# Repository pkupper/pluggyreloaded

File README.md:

# Pluggy Reloaded
Adapter Board for the Gigatron TTL Microcomputer

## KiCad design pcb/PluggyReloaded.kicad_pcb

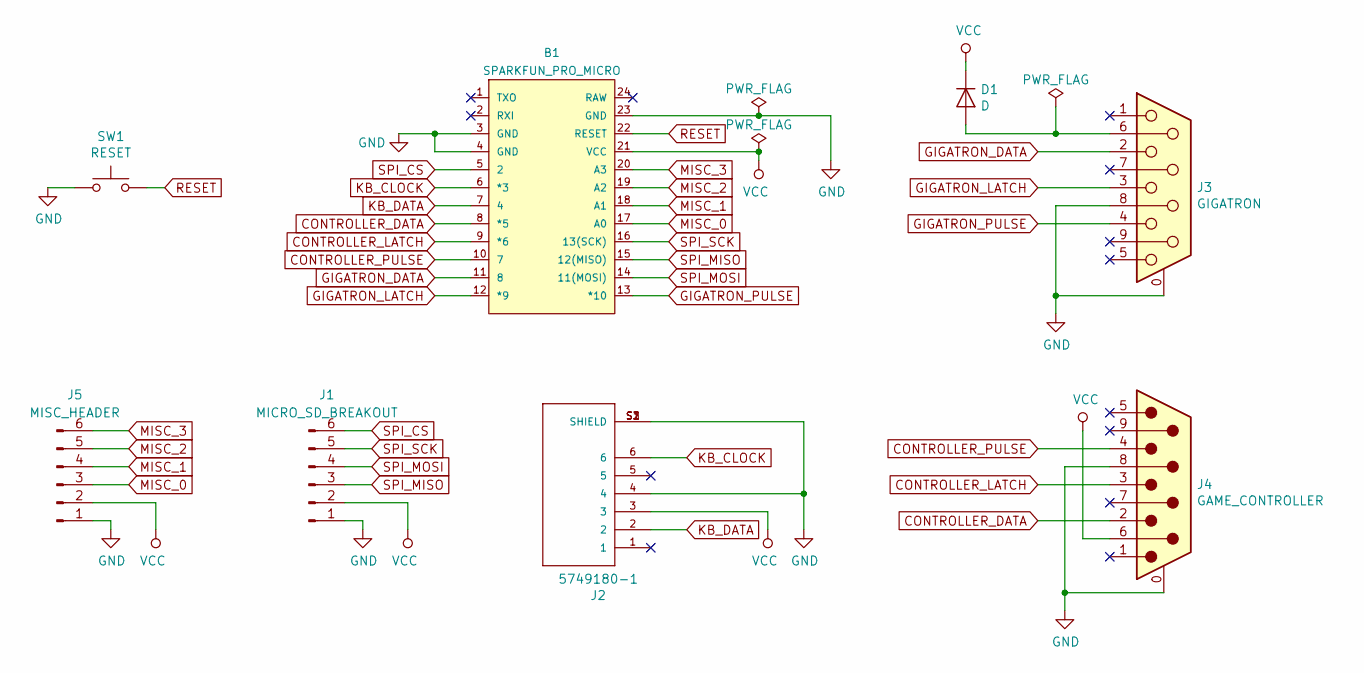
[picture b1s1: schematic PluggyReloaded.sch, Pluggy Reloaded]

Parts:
B1: SPARKFUN_PRO_MICRO
D1: D; D_DO-35_SOD27_P7.62mm_Horizontal
J1: MICRO_SD_BREAKOUT; PinHeader_1x06_P2.54mm_Vertical
J2: 5749180-1; TE_5749180-1
J3: GIGATRON; DSUB-9_Female_Horizontal_P2.77x2.84mm_EdgePinOffset9.90mm_H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
J4: GAME_CONTROLLER; DSUB-9_Male_Horizontal_P2.77x2.84mm_EdgePinOffset9.90mm_Hou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
J5: MISC_HEADER; PinHeader_1x06_P2.54mm_Vertical
SW1: RESET; SW_PUSH_6mm_H5mm

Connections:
CONTROLLER_DATA: B1.8 (*5), J4.2
CONTROLLER_LATCH: B1.9 (*6), J4.3
CONTROLLER_PULSE: B1.10 (7), J4.4
GIGATRON_DATA: B1.11 (8), J3.2
GIGATRON_LATCH: B1.12 (*9), J3.3
GIGATRON_PULSE: B1.13 (*10), J3.4
GND: B1.3 (GND), B1.4 (GND), B1.23 (GND), J1.1, J2.4, J2.S1 (SHIELD), J2.S2 (SHIELD), J2.S3 (SHIELD), J3.0 (PAD), J3.8, J4.0 (PAD), J4.8, J5.1, SW1.1
KB_CLOCK: B1.6 (*3), J2.6
KB_DATA: B1.7 (4), J2.2
MISC_0: B1.17 (A0), J5.3
MISC_1: B1.18 (A1), J5.4
MISC_2: B1.19 (A2), J5.5
MISC_3: B1.20 (A3), J5.6
unnamed: D1.2 (A), J3.6
RESET: B1.22 (RESET), SW1.2
SPI_CS: B1.5 (2), J1.6
SPI_MISO: B1.15 (12(MISO)), J1.3
SPI_MOSI: B1.14 (11(MOSI)), J1.4
SPI_SCK: B1.16 (13(SCK)), J1.5
VCC: B1.21 (VCC), D1.1 (K), J1.2, J2.3, J4.6, J5.2

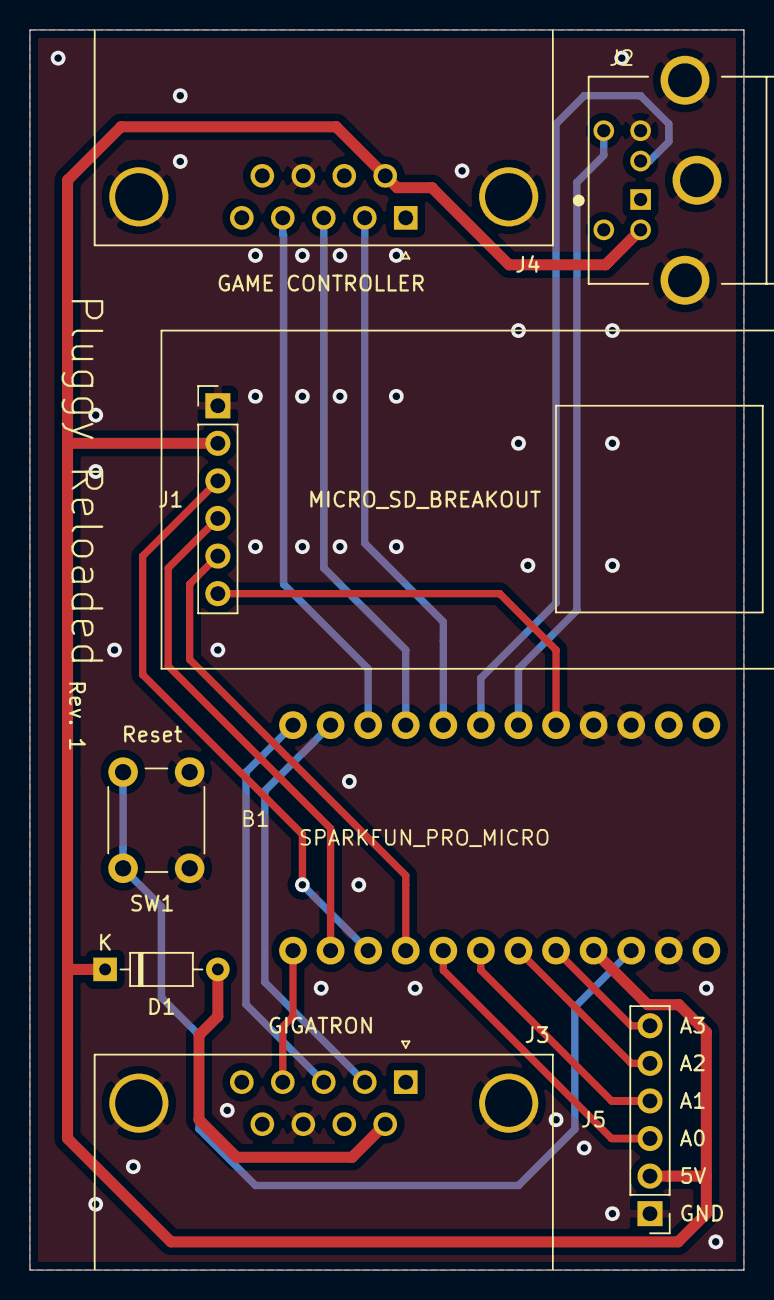
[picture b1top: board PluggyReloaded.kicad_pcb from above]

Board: 2 copper layers, 48.3 x 83.8 mm, 8 parts (0 on the bottom side), 20 nets.

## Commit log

2019-11-27 Add .gitignore for KiCAD Project
2019-11-27 Add KiCad Project
2019-11-27 Add Case Files
2019-11-27 Add LICENSE
2019-11-27 Improve Case tolerances
2019-11-27 More case tweaks
2019-11-28 Update stl files to include recent tweaks
